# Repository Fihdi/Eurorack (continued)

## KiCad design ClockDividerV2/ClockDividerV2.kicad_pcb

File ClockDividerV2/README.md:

An Improved Clockdivider module based on the ATMEGA328P microcontroller instead of the CD4040 binary counter IC. Instead of simply counting in binary, this module can be switched to count in binary, prime numbers and harmonically. I am also thinking about making a fourth mode: Random mode, where at each trigger, the outputs have different probabilities to turning on or off. It's also possible to analyze the incoming clock frequency and output a multiple of the input frequencies to the outputs.

A button press or a rising edge on the input "CLK" will increase the internal counter.

A button press or a rising edge on the input "MODE" will switch to another mode.

A button press or a rising edge on the input "RESET" resets the internal counter of the output states, it does not reset the mode.

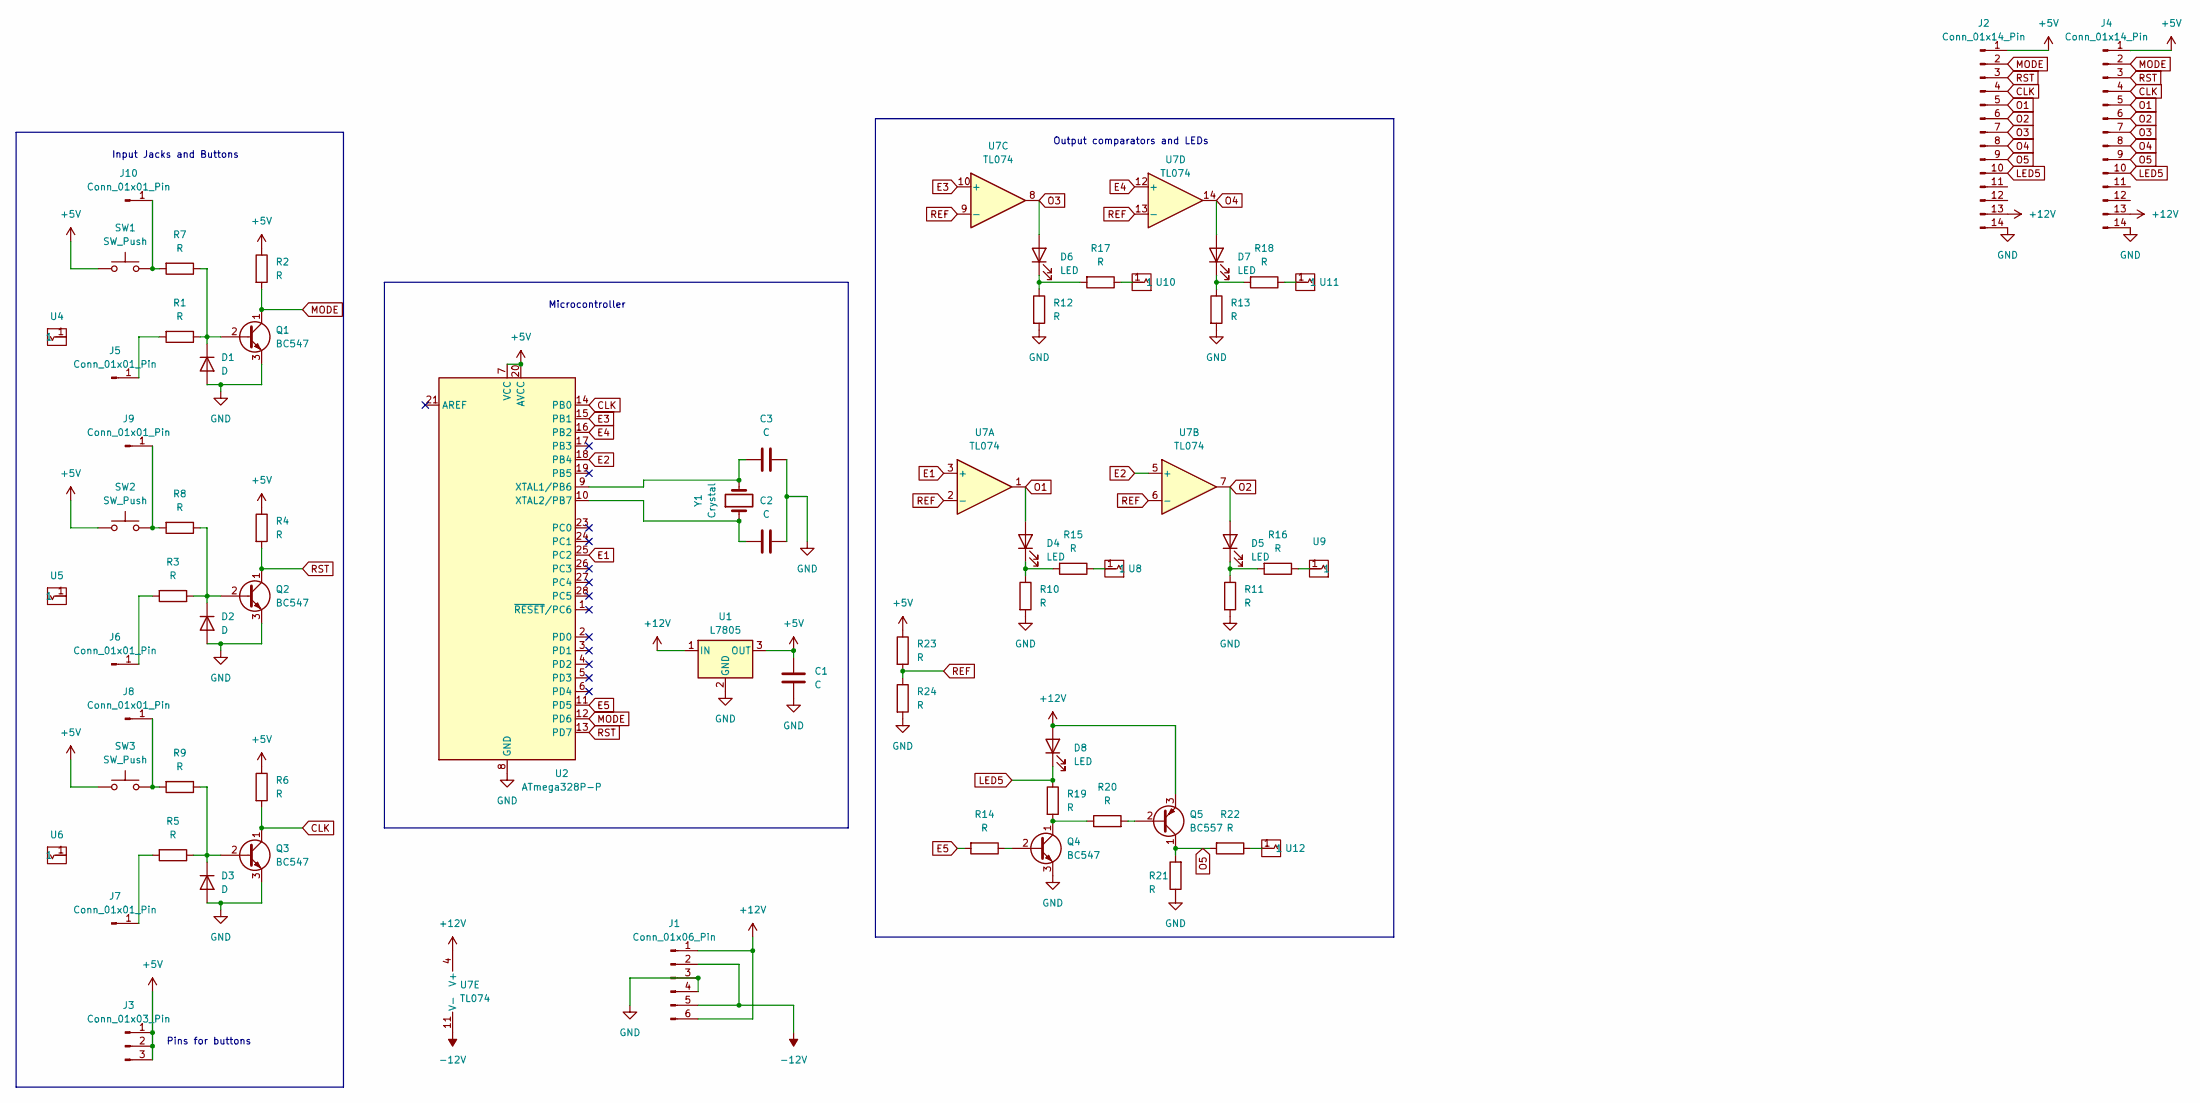
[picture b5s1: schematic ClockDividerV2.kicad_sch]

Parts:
C1: C; C_Rect_L10.3mm_W4.5mm_P7.50mm_MKS4
C2, C3: C; C_Disc_D5.0mm_W2.5mm_P2.50mm
D1, D2, D3: D; D_A-405_P7.62mm_Horizontal
D4, D5, D6, D7, D8: LED; LED_D5.0mm
J1: Conn_01x06_Pin; PinSocket_1x06_P2.54mm_Vertical
J2, J4: Conn_01x14_Pin; PinHeader_1x14_P2.54mm_Vertical
J3: Conn_01x03_Pin; PinHeader_1x03_P2.54mm_Vertical
J5, J6, J7, J8, J9, J10: Conn_01x01_Pin; PinHeader_1x01_P2.00mm_Vertical
Q1, Q2, Q3, Q4: BC547; TO-92_Inline_Wide
Q5: BC557; TO-92L_Inline_Wide
R1, R2, R3, R4, R5, R6, R7, R8, R9, R10, R11, R12, R13, R14, R15, R16, R17, R18, R19, R20, R21, R22, R23, R24: R; R_Axial_DIN0207_L6.3mm_D2.5mm_P7.62mm_Horizontal
SW1, SW2, SW3: SW_Push
U1: L7805; TO-252-3_TabPin2
U2: ATmega328P-P; DIP-28_W7.62mm
U4, U5, U6, U8, U9, U10, U11, U12: Aux_flush; 3mm5 Mono Aux
U7: TL074; DIP-14_W7.62mm
Y1: Crystal; Crystal_HC49-U_Vertical

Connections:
+5V: C1.1, J2.1, J3.1, J3.2, J3.3, J4.1, R2.1, R4.1, R6.1, R23.1, SW1.1, SW2.1, SW3.1, U1.3 (OUT), U2.7 (VCC), U2.20 (AVCC), U4.3
+12V: D8.2 (A), J1.1, J1.6, J2.13, J4.13, Q5.3 (E), U1.1 (IN), U7.4 (V+)
-12V: J1.2, J1.5, U7.11 (V-)
CLK: J2.4, J4.4, Q3.1 (C), R6.2, U2.14 (PB0)
E1: U2.25 (PC2), U7.3 (+)
E2: U2.18 (PB4), U7.5 (+)
E3: U2.15 (PB1), U7.10 (+)
E4: U2.16 (PB2), U7.12 (+)
E5: R14.2, U2.11 (PD5)
GND: C1.2, C2.2, C3.2, D1.2 (A), D2.2 (A), D3.2 (A), J1.3, J1.4, J2.14, J4.14, Q1.3 (E), Q2.3 (E), Q3.3 (E), Q4.3 (E), R10.2, R11.2, R12.2, R13.2, R21.1, R24.2, U1.2 (GND), U2.8 (GND), U2.22 (GND)
LED5: D8.1 (K), J2.10, J4.10, R19.1
MODE: J2.2, J4.2, Q1.1 (C), R2.2, U2.12 (PD6)
unnamed: D1.1 (K), Q1.2 (B), R1.1, R7.1
unnamed: D2.1 (K), Q2.2 (B), R3.1, R8.1
unnamed: D3.1 (K), Q3.2 (B), R5.1, R9.1
unnamed: D4.1 (K), R10.1, R15.2
unnamed: D5.1 (K), R11.1, R16.2
unnamed: D6.1 (K), R12.1, R17.2
unnamed: D7.1 (K), R13.1, R18.2
unnamed: J5.1, R1.2
unnamed: J6.1, R3.2
unnamed: J7.1, R5.2
unnamed: J8.1, R9.2
unnamed: J9.1, R8.2
unnamed: J10.1, R7.2
unnamed: Q4.2 (B), R14.1
unnamed: Q4.1 (C), R19.2, R20.1
unnamed: Q5.2 (B), R20.2
unnamed: R15.1, U8.1
unnamed: R16.1, U9.1
unnamed: R17.1, U10.1
unnamed: R18.1, U11.1
unnamed: R22.1, U12.1
unnamed: C3.1, U2.9 (XTAL1/PB6), Y1.2
unnamed: C2.1, U2.10 (XTAL2/PB7), Y1.1
O1: D4.2 (A), J2.5, J4.5, U7.1
O2: D5.2 (A), J2.6, J4.6, U7.7
O3: D6.2 (A), J2.7, J4.7, U7.8
O4: D7.2 (A), J2.8, J4.8, U7.14
O5: J2.9, J4.9, Q5.1 (C), R21.2, R22.2
REF: R23.2, R24.1, U7.2 (-), U7.6 (-), U7.9 (-), U7.13 (-)
RST: J2.3, J4.3, Q2.1 (C), R4.2, U2.13 (PD7)

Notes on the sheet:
Pins for buttons
Input Jacks and Buttons
Output comparators and LEDs
Microcontroller

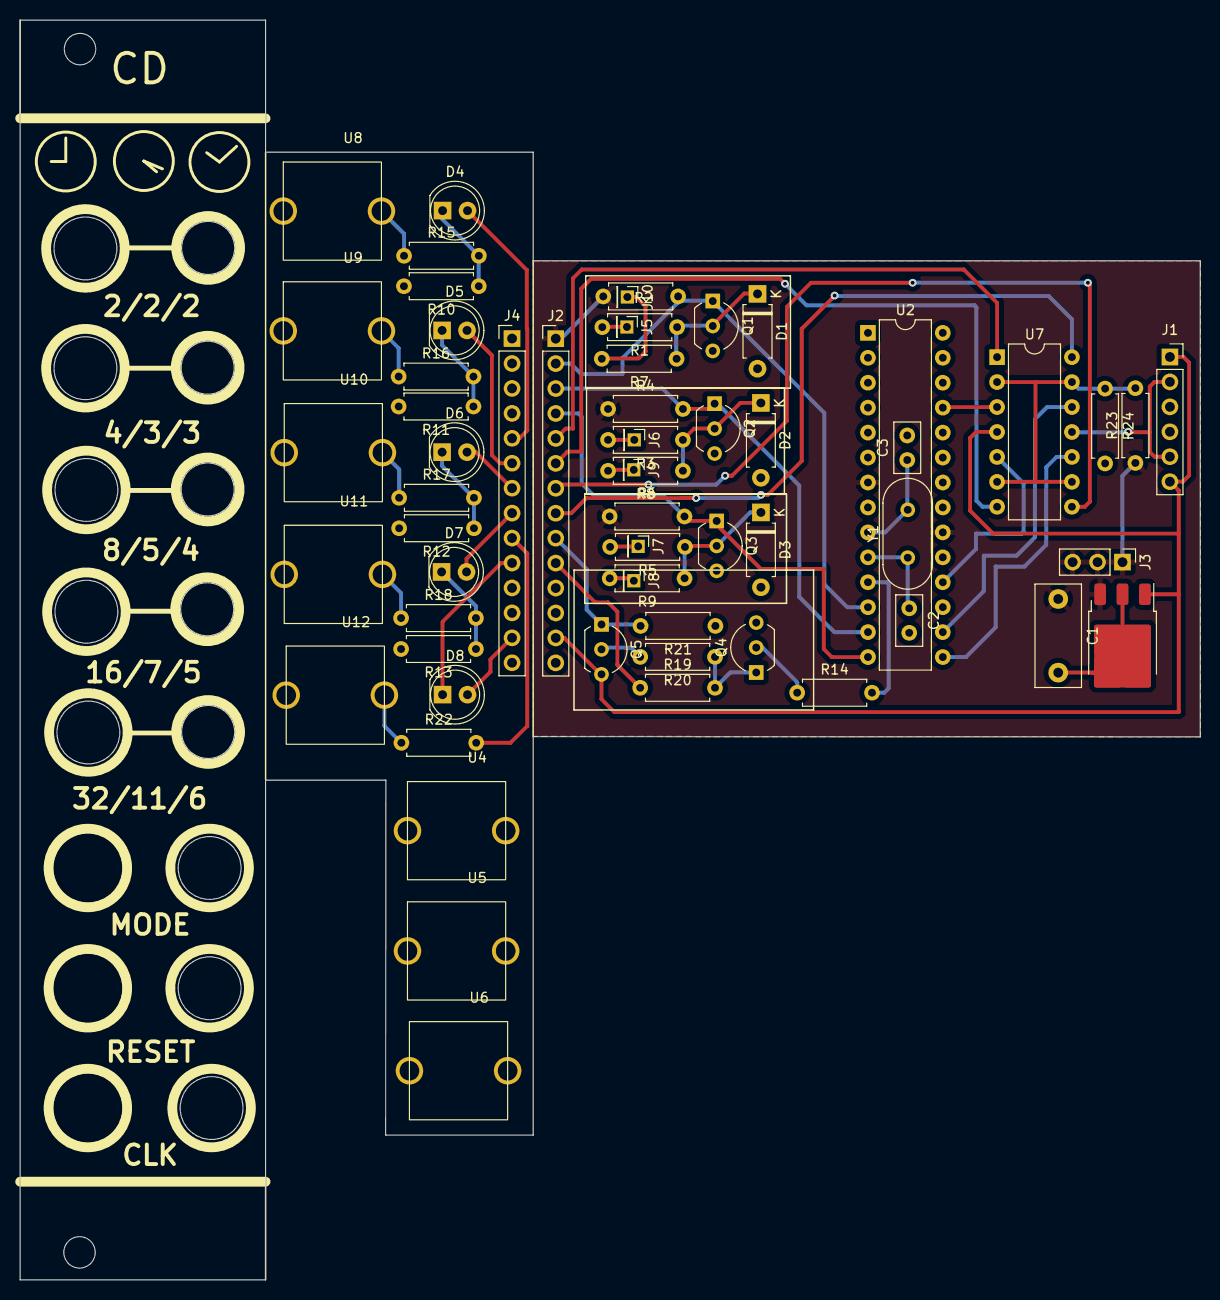
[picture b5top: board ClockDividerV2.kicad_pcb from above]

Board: 2 copper layers, 120.2 x 128.3 mm, 62 parts (0 on the bottom side), 42 nets.

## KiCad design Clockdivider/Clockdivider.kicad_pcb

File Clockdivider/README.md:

CD4040 based Clockdivider with 4 stages and Reset input.

No Output Resistors. No Input Trigger conditioners thus the module only triggers with strong gates.

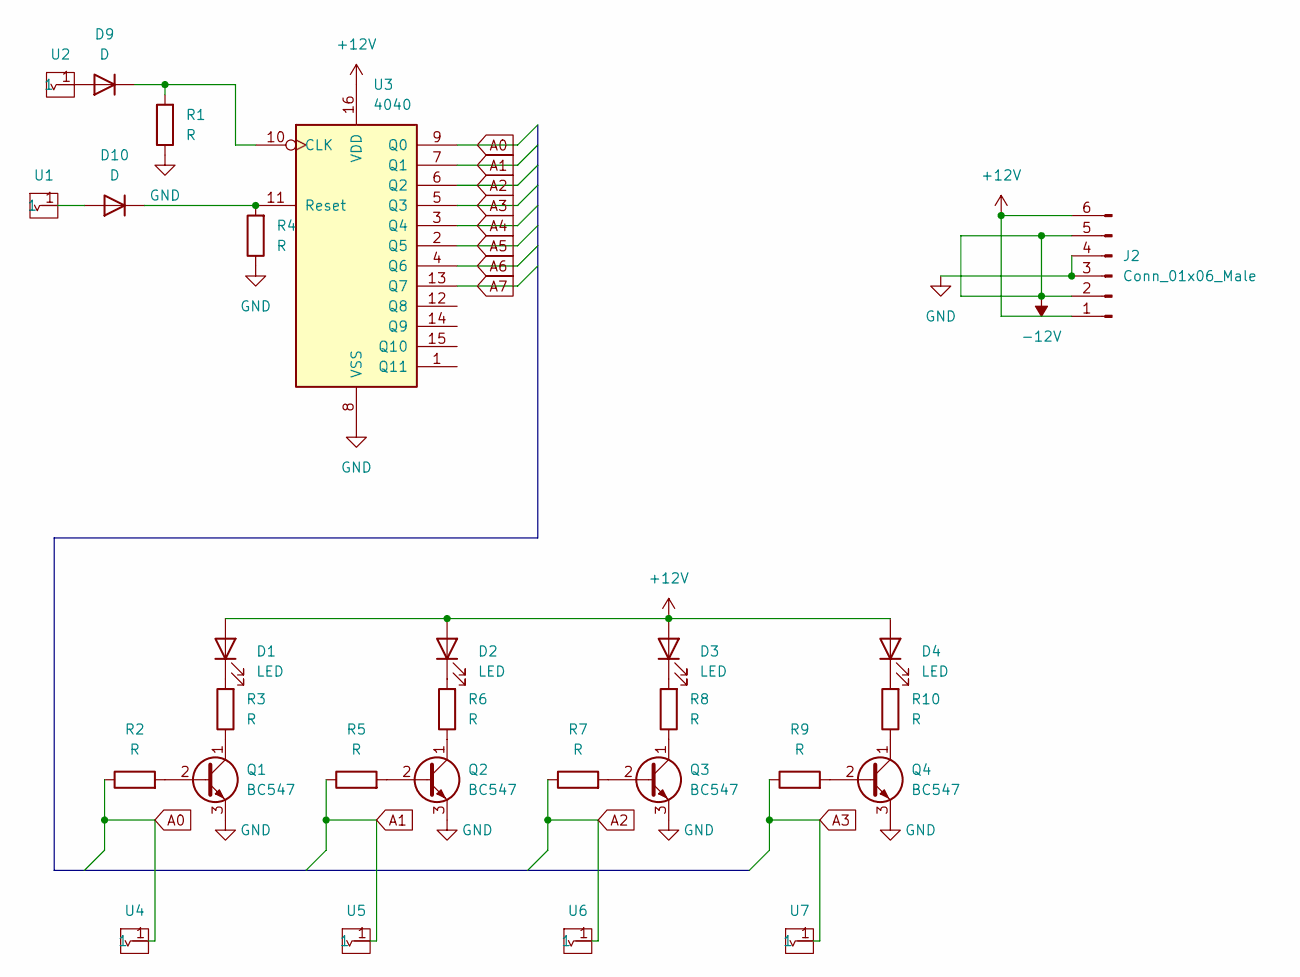
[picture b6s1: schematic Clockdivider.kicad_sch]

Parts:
D1, D2, D3, D4: LED; LED_D5.0mm
D9, D10: D; D_A-405_P7.62mm_Horizontal
J2: Conn_01x06_Male; JST_EH_B6B-EH-A_1x06_P2.50mm_Vertical
Q1, Q2, Q3, Q4: BC547; TO-92S_Wide
R1, R2, R3, R4, R5, R6, R7, R8, R9, R10: R; R_Axial_DIN0207_L6.3mm_D2.5mm_P7.62mm_Horizontal
U1, U2, U4, U5, U6, U7: Aux_flush; aux_flush
U3: 4040; DIP-16_W7.62mm_Socket

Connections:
+12V: D1.2 (A), D2.2 (A), D3.2 (A), D4.2 (A), J2.1, J2.6, U3.16 (VDD)
-12V: J2.2, J2.5
A0: R2.1, U3.9 (Q0), U4.1
A1: R5.1, U3.7 (Q1), U5.1
A2: R7.1, U3.6 (Q2), U6.1
A3: R9.1, U3.5 (Q3), U7.1
A4: U3.3 (Q4)
A5: U3.2 (Q5)
A6: U3.4 (Q6)
A7: U3.13 (Q7)
GND: J2.3, J2.4, Q1.3 (E), Q2.3 (E), Q3.3 (E), Q4.3 (E), R1.1, R4.1, U3.8 (VSS)
unnamed: D1.1 (K), R3.2
unnamed: D2.1 (K), R6.2
unnamed: D3.1 (K), R8.2
unnamed: D4.1 (K), R10.2
unnamed: D9.1 (K), R1.2, U3.10 (CLK)
unnamed: D9.2 (A), U2.1
unnamed: D10.1 (K), R4.2, U3.11 (Reset)
unnamed: D10.2 (A), U1.1
unnamed: Q1.1 (C), R3.1
unnamed: Q1.2 (B), R2.2
unnamed: Q2.1 (C), R6.1
unnamed: Q2.2 (B), R5.2
unnamed: Q3.1 (C), R8.1
unnamed: Q3.2 (B), R7.2
unnamed: Q4.1 (C), R10.1
unnamed: Q4.2 (B), R9.2

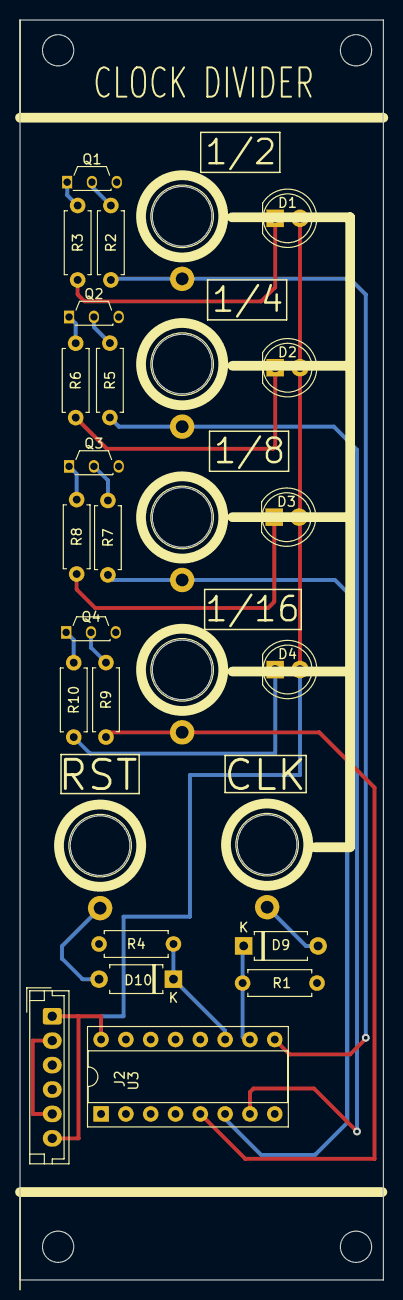
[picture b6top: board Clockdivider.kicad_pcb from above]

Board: 2 copper layers, 37.2 x 129.0 mm, 28 parts (0 on the bottom side), 23 nets.

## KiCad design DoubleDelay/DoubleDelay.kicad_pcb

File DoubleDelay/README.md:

Simple delay module with two identical PT2399 circuits either in series or separate. Parameters for Level, Delay Time, and Feedback amount can be set with knobs.
This module features no CV.

Ideas for a new module:

I was thinking about a "SingleDelay" module (in contrast to the "DoubleDelay") where
the three parameters for level, time and feedback can be voltage controlled.

For Level CV, the PT2399 output is fed back through a VCA.
For Time CV, a 470 to 1k resistor with an NPN transistor for biasing can be used.
For Feedback CV, like with level, the PT2399 output is fed back through a separate VCA back to the Input summing amplifier for the PT2399 input.

Another feature idea would be to only let the delayed sound through. 
This can be achieved by adding an attenuation knob for the input signal on the output summing stage. 
Instead of a knob a switch could be used to bypass the signal instead of attenuation.

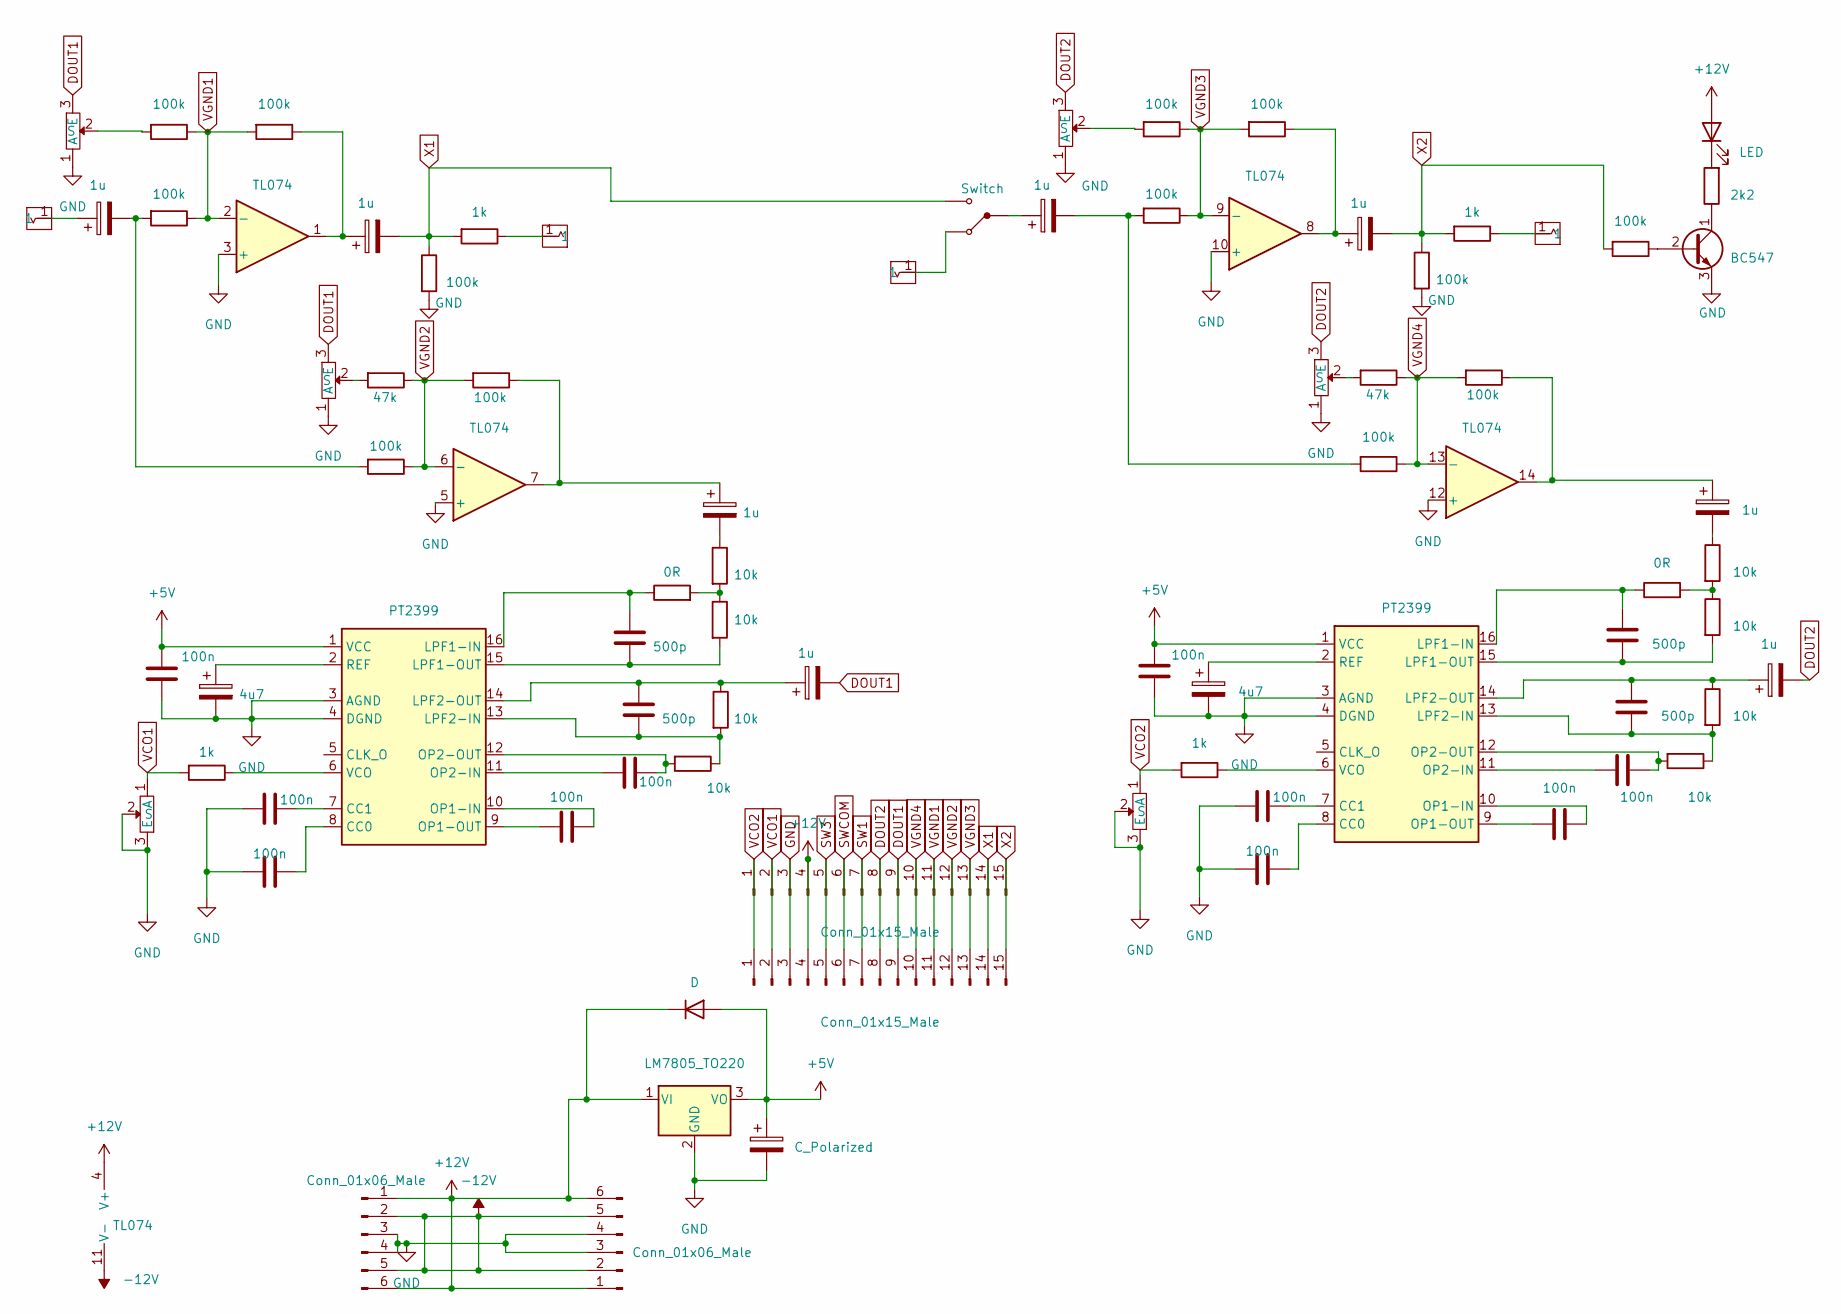
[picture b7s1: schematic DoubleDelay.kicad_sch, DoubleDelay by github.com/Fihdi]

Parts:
C1, C3, C4, C7, C9, C15, C17, C18, C20, C22: 100n; C_Axial_L3.8mm_D2.6mm_P7.50mm_Horizontal
C2, C16: 4u7; C_Rect_L9.0mm_W2.7mm_P7.50mm_MKT
C5, C6, C11, C13, C14, C19, C24, C25: 1u; C_Rect_L9.0mm_W2.7mm_P7.50mm_MKT
C8, C10, C21, C23: 500p; C_Axial_L3.8mm_D2.6mm_P7.50mm_Horizontal
C12: C_Polarized; CP_Radial_D10.0mm_P3.80mm
D1: D; D_A-405_P7.62mm_Horizontal
D3: LED; LED_D5.0mm
J1, J2: Conn_01x06_Male; PinHeader_1x06_P2.54mm_Vertical
J3, J4: Conn_01x15_Male; PinHeader_1x15_P2.54mm_Vertical
Q2: BC547; TO-92_Inline_Wide
R1, R2, R14, R19, R20, R25: AlpsPot
R3, R9, R23, R29: 1k; R_Axial_DIN0207_L6.3mm_D2.5mm_P7.62mm_Horizontal
R4, R5, R6, R7, R17, R18, R21, R22, R24, R27, R28, R30, R31: 100k; R_Axial_DIN0207_L6.3mm_D2.5mm_P7.62mm_Horizontal
R8, R10, R11, R12, R32, R34, R35, R36: 10k; R_Axial_DIN0207_L6.3mm_D2.5mm_P7.62mm_Horizontal
R16, R26: 47k; R_Axial_DIN0207_L6.3mm_D2.5mm_P7.62mm_Horizontal
R33: 2k2; R_Axial_DIN0207_L6.3mm_D2.5mm_P7.62mm_Horizontal
R37, R39: 0R; R_Axial_DIN0207_L6.3mm_D2.5mm_P7.62mm_Horizontal
U1, U4, U6, U10: Aux_flush; 3mm5 Mono Aux
U2: TL074; DIP-14_W7.62mm
U3, U9: PT2399; DIP-16_W7.62mm
U5: LM7805_TO220; TO-220-3_Vertical
U7: Switch

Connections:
+5V: C1.1, C12.1, C15.1, D1.2 (A), U3.1 (VCC), U5.3 (VO), U9.1 (VCC)
+12V: D1.1 (K), D3.2 (A), J1.1, J1.6, J2.1, J2.6, J3.4, J4.4, U2.4 (V+), U5.1 (VI)
-12V: J1.2, J1.5, J2.2, J2.5, U2.11 (V-)
DOUT1: C11.2, J3.9, J4.9, R2.3 (E), R14.3 (E)
DOUT2: C25.2, J3.8, J4.8, R19.3 (E), R25.3 (E)
GND: C1.2, C2.2, C3.1, C4.1, C12.2, C15.2, C16.2, C17.1, C18.1, J1.3, J1.4, J2.3, J2.4, J3.3, J4.3, Q2.3 (E), R1.2 (S), R1.3 (E), R2.1 (A), R7.2, R14.1 (A), R19.1 (A), R20.2 (S), R20.3 (E), R25.1 (A), R28.2, U2.3 (+), U2.5 (+), U2.10 (+), U2.12 (+), U3.3 (AGND), U3.4 (DGND), U5.2 (GND), U9.3 (AGND), U9.4 (DGND)
unnamed: C5.1, R6.1, U2.1
unnamed: C6.1, R18.1, U2.7
unnamed: C6.2, R10.1
unnamed: C13.1, U1.1
unnamed: C13.2, R5.2, R17.2
unnamed: C14.1, U7.2
unnamed: C14.2, R22.2, R27.2
unnamed: C19.1, R24.1, U2.8
unnamed: C24.1, R30.1, U2.14
unnamed: C24.2, R34.1
unnamed: D3.1 (K), R33.2
unnamed: Q2.2 (B), R31.1
unnamed: Q2.1 (C), R33.1
unnamed: R2.2 (S), R4.2
unnamed: R9.1, U4.1
unnamed: R10.2, R11.1, R37.2
unnamed: R14.2 (S), R16.2
unnamed: R19.2 (S), R21.2
unnamed: R25.2 (S), R26.2
unnamed: R29.1, U10.1
unnamed: R34.2, R35.1, R39.2
unnamed: C4.2, U3.8 (CC0)
unnamed: C3.2, U3.7 (CC1)
unnamed: C8.1, R37.1, U3.16 (LPF1-IN)
unnamed: C8.2, R11.2, U3.15 (LPF1-OUT)
unnamed: C10.2, R8.1, R12.2, U3.13 (LPF2-IN)
unnamed: C10.1, C11.1, R12.1, U3.14 (LPF2-OUT)
unnamed: C7.2, U3.10 (OP1-IN)
unnamed: C7.1, U3.9 (OP1-OUT)
unnamed: C9.1, U3.11 (OP2-IN)
unnamed: C9.2, R8.2, U3.12 (OP2-OUT)
unnamed: C2.1, U3.2 (REF)
unnamed: R3.1, U3.6 (VCO)
unnamed: U6.1, U7.1
unnamed: C18.2, U9.8 (CC0)
unnamed: C17.2, U9.7 (CC1)
unnamed: C21.1, R39.1, U9.16 (LPF1-IN)
unnamed: C21.2, R35.2, U9.15 (LPF1-OUT)
unnamed: C23.2, R32.1, R36.2, U9.13 (LPF2-IN)
unnamed: C23.1, C25.1, R36.1, U9.14 (LPF2-OUT)
unnamed: C20.2, U9.10 (OP1-IN)
unnamed: C20.1, U9.9 (OP1-OUT)
unnamed: C22.1, U9.11 (OP2-IN)
unnamed: C22.2, R32.2, U9.12 (OP2-OUT)
unnamed: C16.1, U9.2 (REF)
unnamed: R23.1, U9.6 (VCO)
SW1: J3.7, J4.7
SW3: J3.5, J4.5
SWCOM: J3.6, J4.6
VCO1: J3.2, J4.2, R1.1 (A), R3.2
VCO2: J3.1, J4.1, R20.1 (A), R23.2
VGND1: J3.11, J4.11, R4.1, R5.1, R6.2, U2.2 (-)
VGND2: J3.12, J4.12, R16.1, R17.1, R18.2, U2.6 (-)
VGND3: J3.13, J4.13, R21.1, R22.1, R24.2, U2.9 (-)
VGND4: J3.10, J4.10, R26.1, R27.1, R30.2, U2.13 (-)
X1: C5.2, J3.14, J4.14, R7.1, R9.2, U7.3
X2: C19.2, J3.15, J4.15, R28.1, R29.2, R31.2

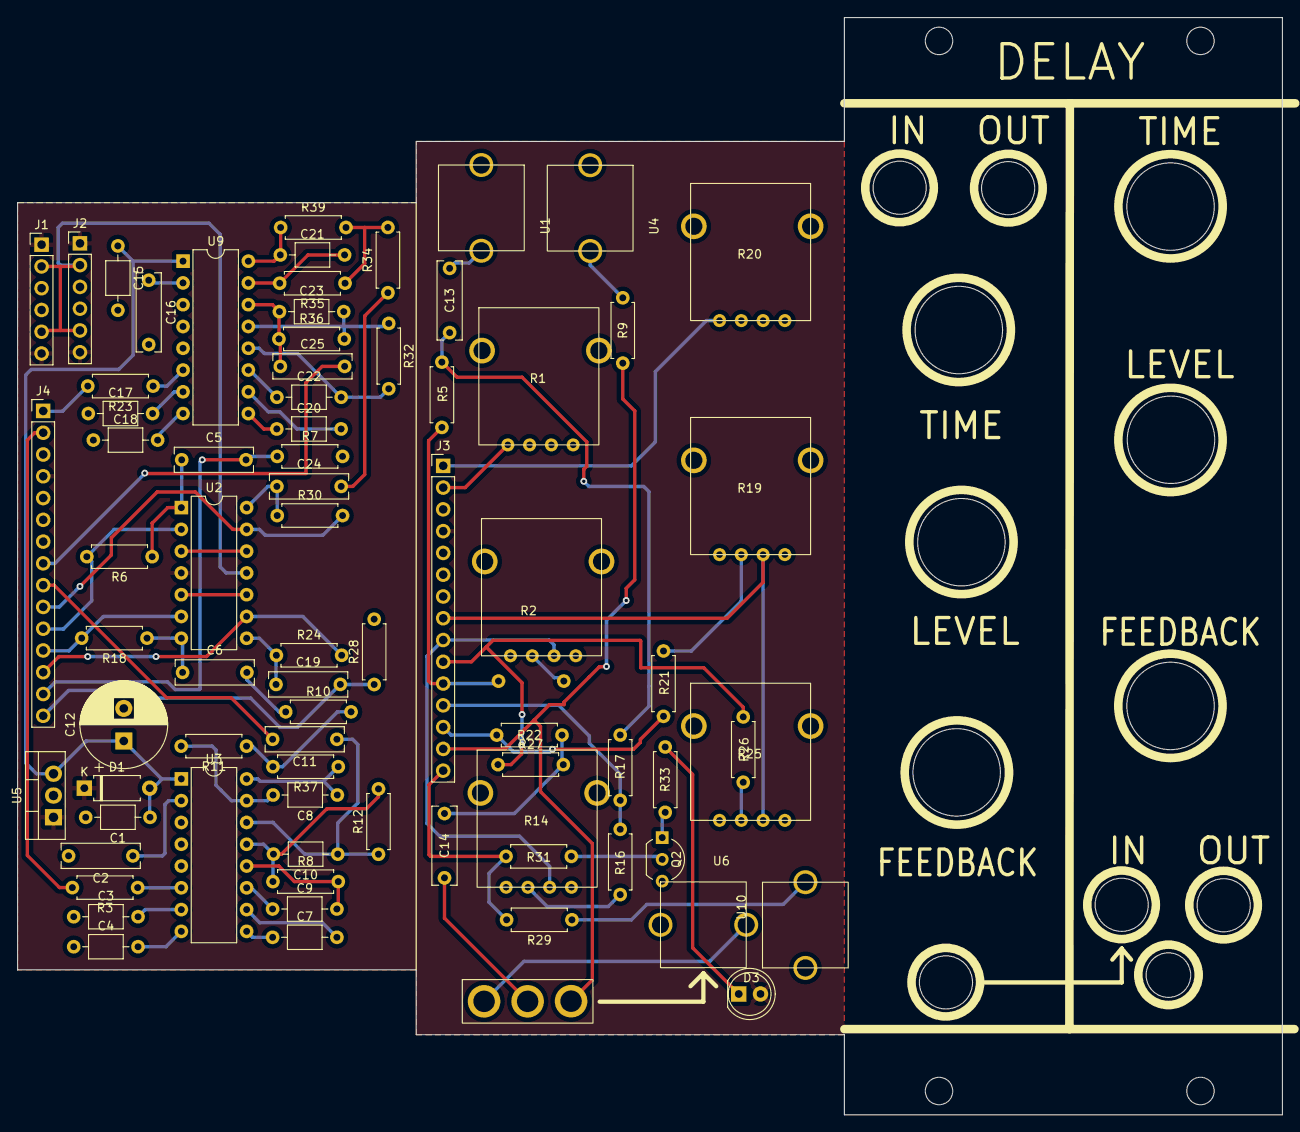
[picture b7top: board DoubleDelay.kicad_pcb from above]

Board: 2 copper layers, 147.6 x 128.0 mm, 77 parts (1 on the bottom side), 63 nets.
